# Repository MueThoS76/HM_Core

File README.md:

# HM_Core

   Bestelliste:
   https://www.develektro.com/index.php?wlid=e9af5fefece089a590443dfd25b689d9&jtl=w

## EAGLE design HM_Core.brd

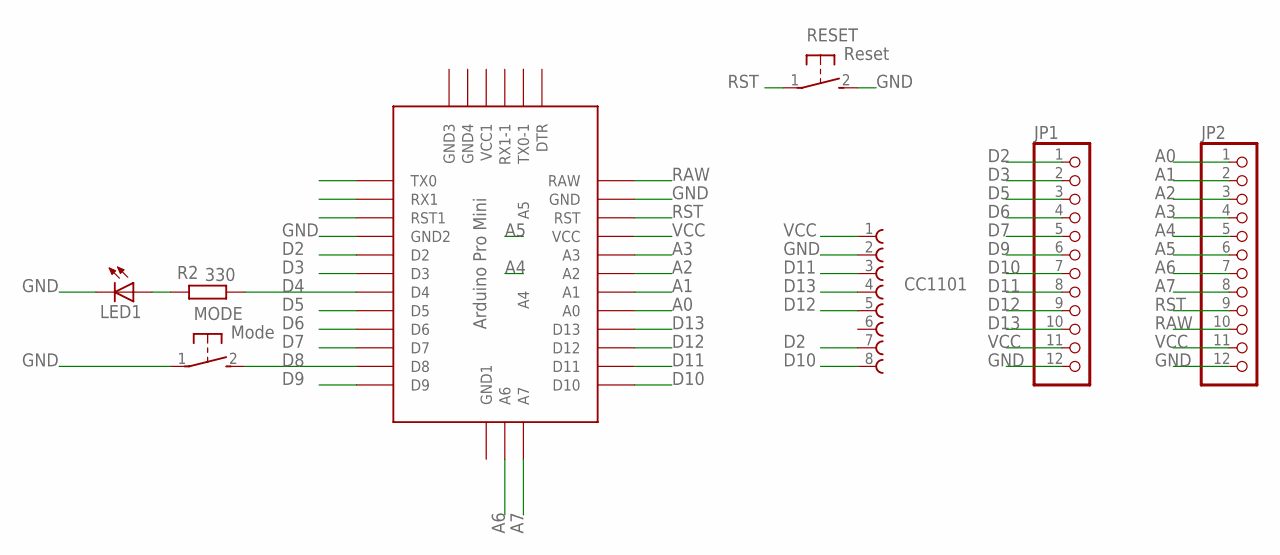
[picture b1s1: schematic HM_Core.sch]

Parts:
CC1101: 62000811121
JP1, JP2: PINHD-1X12; 1X12
LED1: LED3MM
MODE: Mode; B3F-31XX
R2: 330; 0207/10
RESET: Reset; B3F-31XX
U$1: ABK-PRO-MINI

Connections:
A0: JP2.1, U$1.A0
A1: JP2.2, U$1.A1
A2: JP2.3, U$1.A2
A3: JP2.4, U$1.A3
A4: JP2.5, U$1.A4
A5: JP2.6, U$1.A5
A6: JP2.7, U$1.A6
A7: JP2.8, U$1.A7
D2: CC1101.7, JP1.1, U$1.D2
D3: JP1.2, U$1.D3
D4: R2.1, U$1.D4
D5: JP1.3, U$1.D5
D6: JP1.4, U$1.D6
D7: JP1.5, U$1.D7
D8: MODE.2 (S), U$1.D8
D9: JP1.6, U$1.D9
D10: CC1101.8, JP1.7, U$1.D10
D11: CC1101.3, JP1.8, U$1.D11
D12: CC1101.5, JP1.9, U$1.D12
D13: CC1101.4, JP1.10, U$1.D13
GND: CC1101.2, JP1.12, JP2.12, LED1.K (C), MODE.1, RESET.2 (S), U$1.GND, U$1.GND1 (GND2)
unnamed: LED1.A, R2.2
RAW: JP2.10, U$1.RAW
RST: JP2.9, RESET.1, U$1.RST
VCC: CC1101.1, JP1.11, JP2.11, U$1.VCC

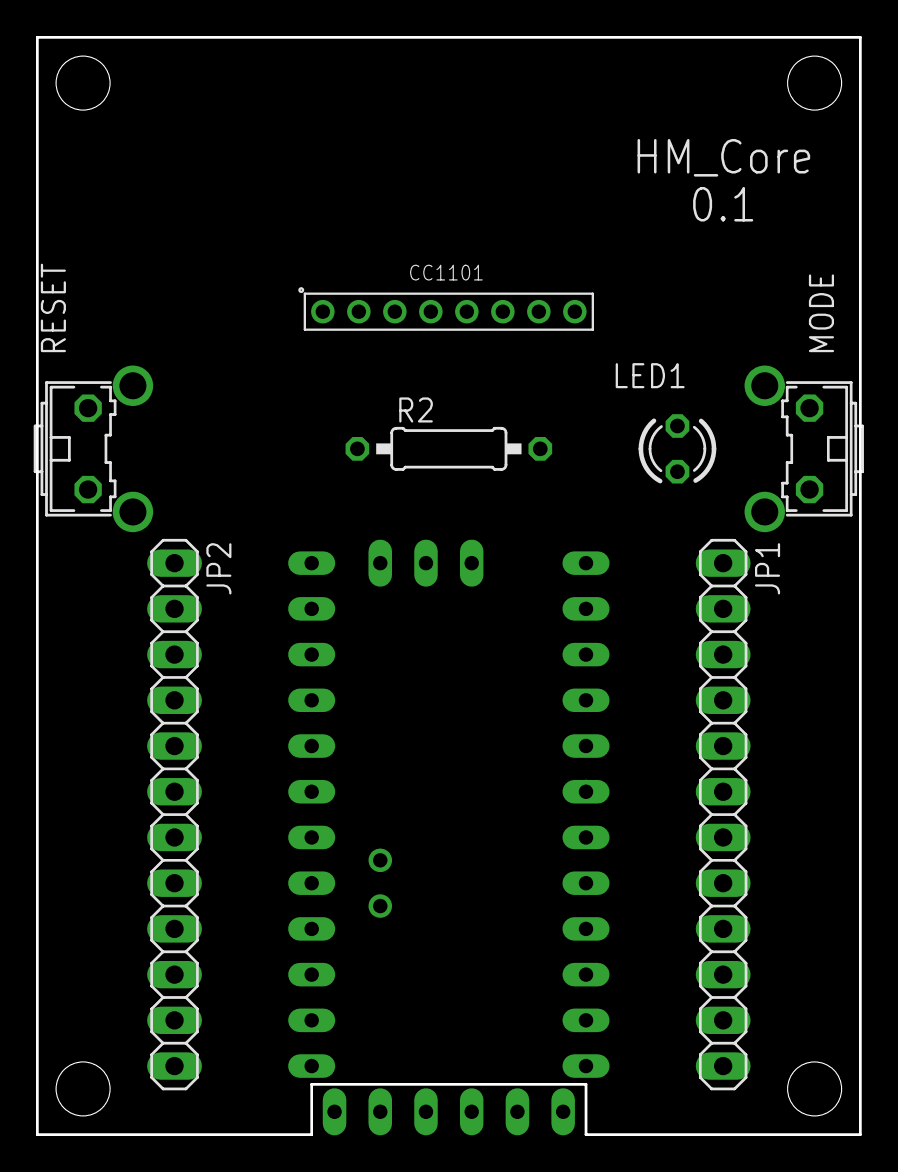
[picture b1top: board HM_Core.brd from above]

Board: 2 copper layers, 45.7 x 61.0 mm, 8 parts (0 on the bottom side), 25 nets.

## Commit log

2019-01-04 Verbesserungen
    Taster zur seite raus
2019-01-04 Anpassungen

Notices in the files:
parts and their libraries:
Wurth_Elektronik_Electromechanic_Board_t: Copyright: Würth Elektronik
